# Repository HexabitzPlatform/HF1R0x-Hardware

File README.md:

# HF1R0x-Hardware
Hexabitz Raspberry Pi Interface Module Hardware Design

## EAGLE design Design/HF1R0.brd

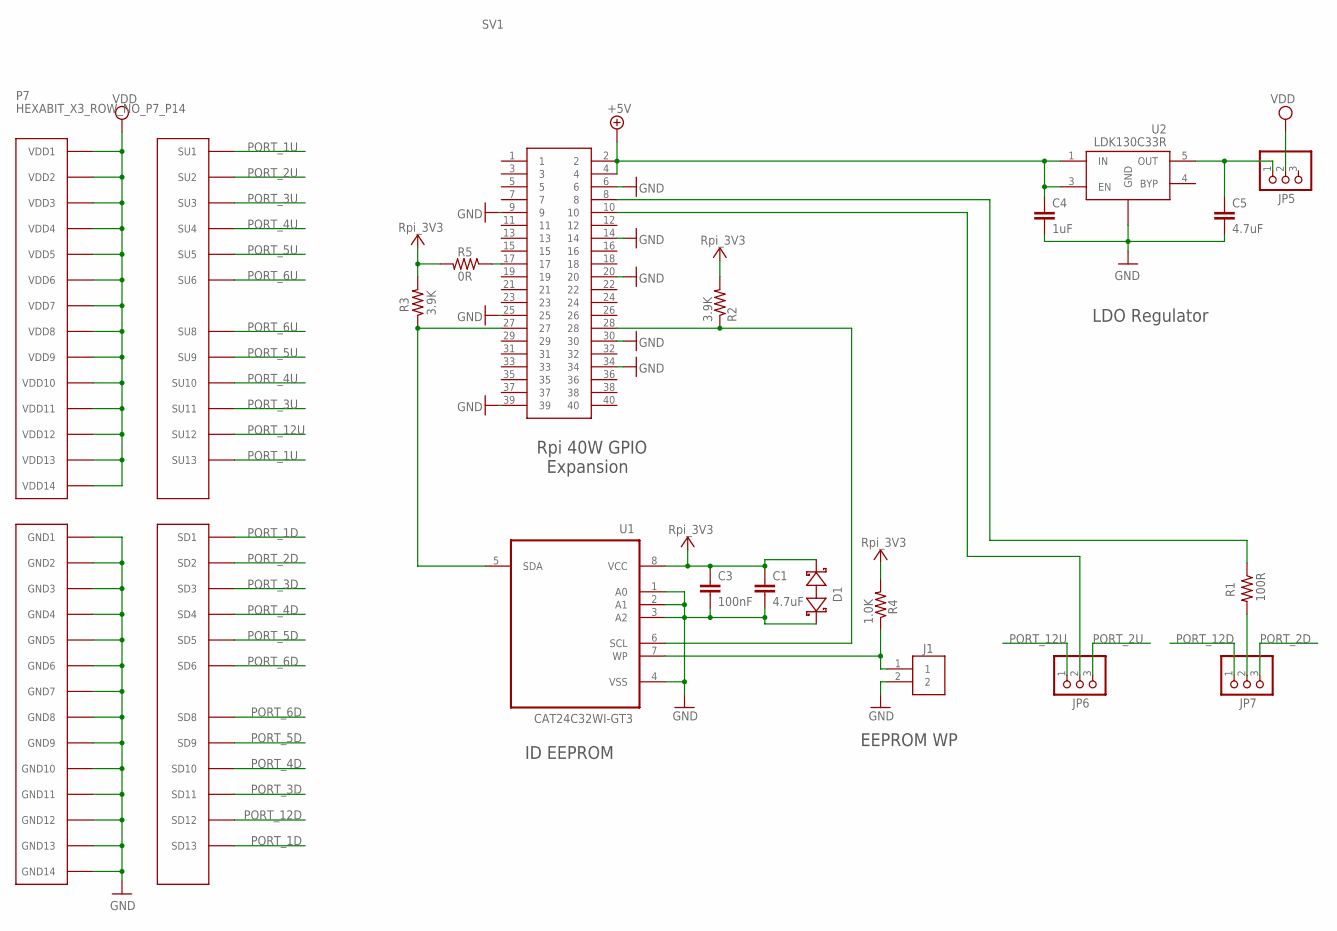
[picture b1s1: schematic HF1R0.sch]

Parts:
C1, C5: 4.7uF; C-0805
C3: 100nF; C-0603; TOLERANCE 10V; VOLTAGE_RATING 10%; MPN C0603C104K8RACTU
C4: 1uF; C-0805
D1: BOURNS_CDSOD323-T03SCBOURNS_CDSOD323-T03SC_0_0; BOURNS_CDSOD323-T03SC_0
J1: 3-644456-2; TE_3-644456-2
JP5, JP6, JP7: PINHD-1X3; 1X03
P7: HEXABIT_X3_ROW_NO_P7_P14
R1: 100R; R-0603; TOLERANCE 1%; MPN ERJ-PA3F1000V
R2, R3: 3.9K; R-0603; TOLERANCE 1%; MPN CRCW06033K90FKEA
R4: 1.0K; R-0603; TOLERANCE 1%; MPN ERJ-3EKF1001V
R5: 0R; R-0603; TOLERANCE 1%; MPN CRCW06033K90FKEA
SV1: PPTC202LFBN-RC; RHDR40W64P254X254_2X20_5105X50; MPN1 PPTC202LFBN-RC
TRIMBLE-LOGO2: HEXABITZ-LOGO
U1: CAT24C32WI-GT3; SOIC127P600X175-8N
U2: LDK130C33R; SOT65P210X110-5N

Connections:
+3V3: C1.1, C3.1, D1.2 (C), R2.2, R3.2, R4.2, R5.2, U1.8 (VCC)
+5V: C4.1, SV1.2, SV1.4, U2.1 (IN), U2.3 (EN)
GND: C1.2, C3.2, C4.2, C5.2, D1.1 (A), J1.2, P7.PAD_PD15 (GND1), P7.PAD_PD16 (GND2), P7.PAD_PD17 (GND3), P7.PAD_PD18 (GND4), P7.PAD_PD19 (GND5), P7.PAD_PD20 (GND6), P7.PAD_PD21 (GND7), P7.PAD_PD22 (GND8), P7.PAD_PD23 (GND9), P7.PAD_PD24 (GND10), P7.PAD_PD25 (GND11), P7.PAD_PD26 (GND12), P7.PAD_PD27 (GND13), P7.PAD_PD28 (GND14), SV1.6, SV1.9, SV1.14, SV1.20, SV1.25, SV1.30, SV1.34, SV1.39, U1.1 (A0), U1.2 (A1), U1.3 (A2), U1.4 (VSS), U2.2 (GND)
ID_SC: R2.1, SV1.28, U1.6 (SCL)
ID_SD: R3.1, SV1.27, U1.5 (SDA)
unnamed: JP7.2, R1.2
unnamed: J1.1, R4.1, U1.7 (WP)
unnamed: R5.1, SV1.17
unnamed: C5.1, JP5.1, U2.5 (OUT)
PORT_1D: P7.PAD_PD1 (SD1), P7.PAD_PD13 (SD13)
PORT_1U: P7.PAD_PU1 (SU1), P7.PAD_PU13 (SU13)
PORT_2D: JP7.3, P7.PAD_PD2 (SD2)
PORT_2U: JP6.3, P7.PAD_PU2 (SU2)
PORT_3D: P7.PAD_PD3 (SD3), P7.PAD_PD11 (SD11)
PORT_3U: P7.PAD_PU3 (SU3), P7.PAD_PU11 (SU11)
PORT_4D: P7.PAD_PD4 (SD4), P7.PAD_PD10 (SD10)
PORT_4U: P7.PAD_PU4 (SU4), P7.PAD_PU10 (SU10)
PORT_5D: P7.PAD_PD5 (SD5), P7.PAD_PD9 (SD9)
PORT_5U: P7.PAD_PU5 (SU5), P7.PAD_PU9 (SU9)
PORT_6D: P7.PAD_PD6 (SD6), P7.PAD_PD8 (SD8)
PORT_6U: P7.PAD_PU6 (SU6), P7.PAD_PU8 (SU8)
PORT_12D: JP7.1, P7.PAD_PD12 (SD12)
PORT_12U: JP6.1, P7.PAD_PU12 (SU12)
RXD0: JP6.2, SV1.10
TXD0: R1.1, SV1.8
VDD: JP5.2, P7.PAD_PU15 (VDD1), P7.PAD_PU16 (VDD2), P7.PAD_PU17 (VDD3), P7.PAD_PU18 (VDD4), P7.PAD_PU19 (VDD5), P7.PAD_PU20 (VDD6), P7.PAD_PU21 (VDD7), P7.PAD_PU22 (VDD8), P7.PAD_PU23 (VDD9), P7.PAD_PU24 (VDD10), P7.PAD_PU25 (VDD11), P7.PAD_PU26 (VDD12), P7.PAD_PU27 (VDD13), P7.PAD_PU28 (VDD14)

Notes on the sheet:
Rpi 40W GPIO Expansion
ID EEPROM
EEPROM WP
LDO Regulator

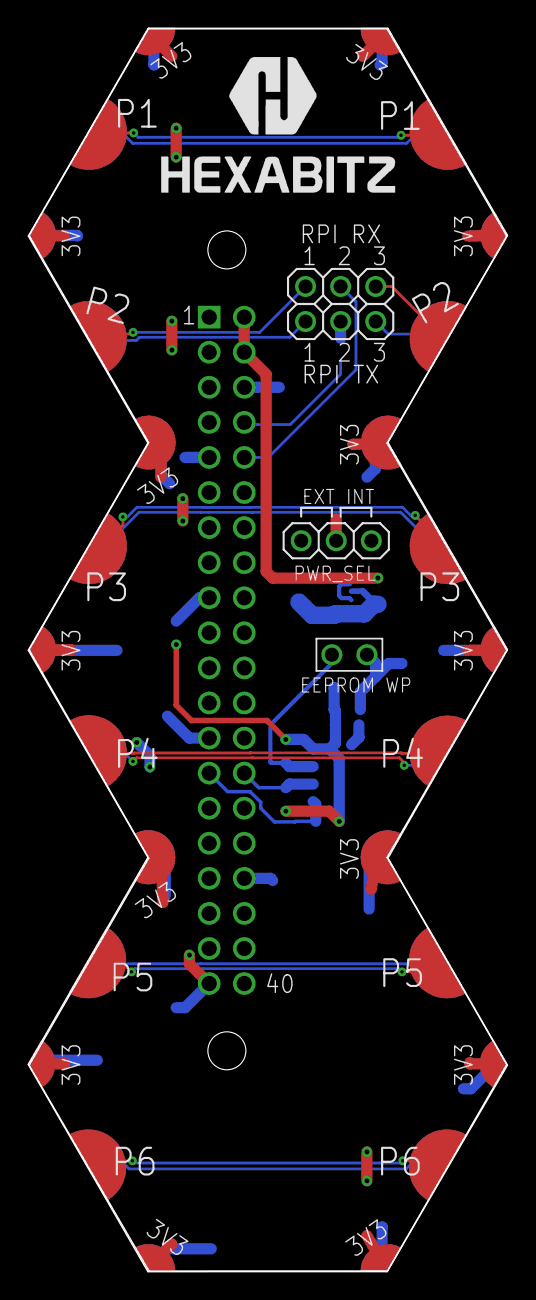
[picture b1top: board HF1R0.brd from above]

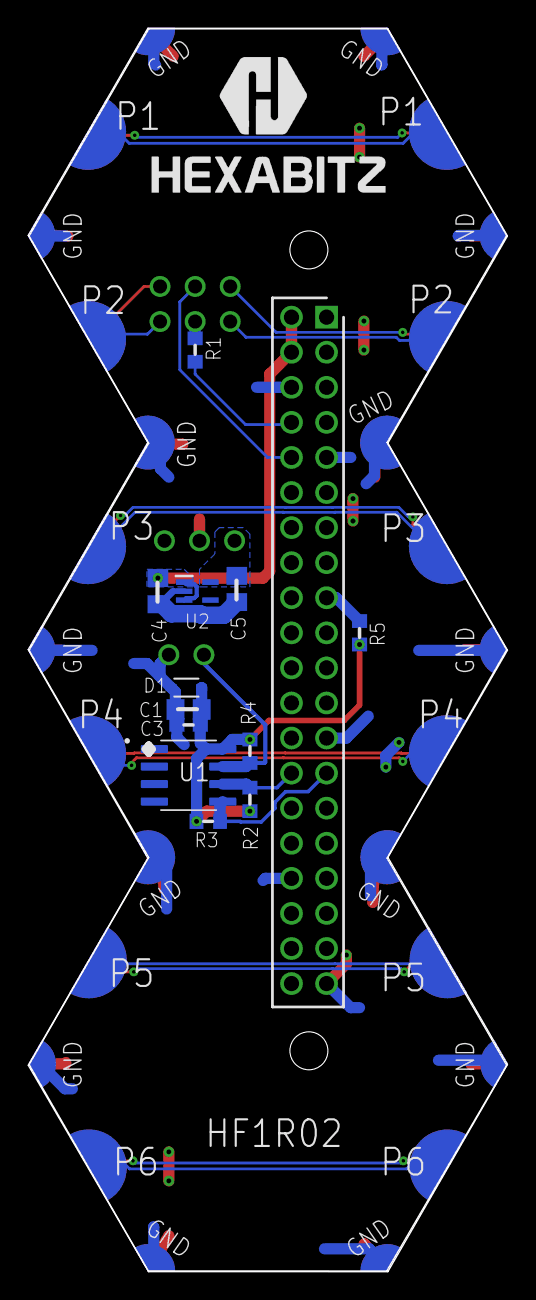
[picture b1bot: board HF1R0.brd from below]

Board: 2 copper layers, 34.7 x 90.0 mm, 19 parts (12 on the bottom side), 26 nets.

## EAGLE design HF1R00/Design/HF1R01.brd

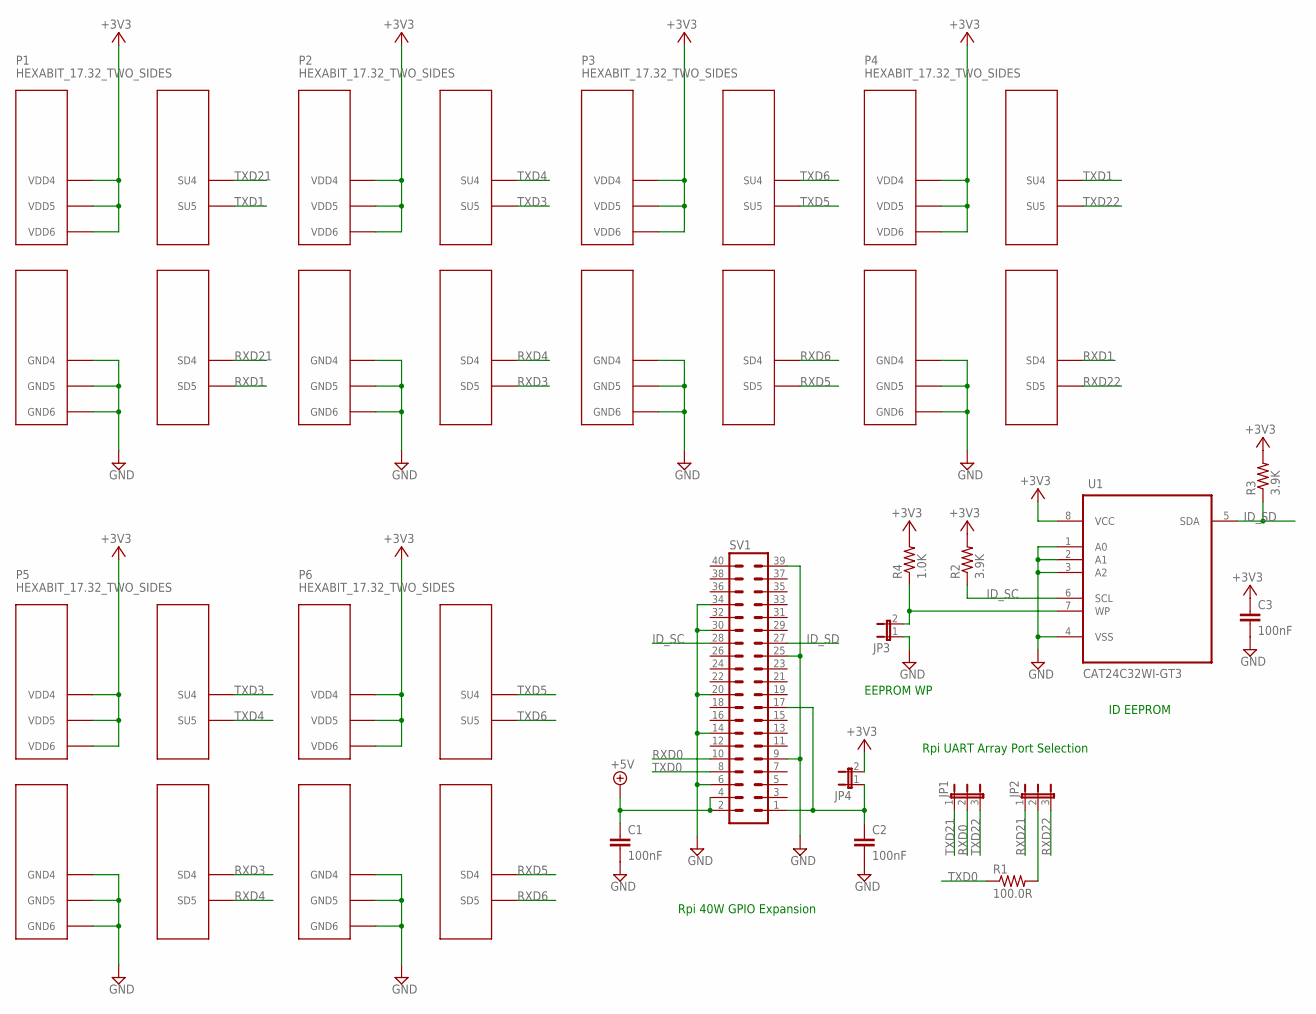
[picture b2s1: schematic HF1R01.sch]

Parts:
C1, C2, C3: 100nF; C-0603; TOLERANCE 10V; VOLTAGE_RATING 10%; MPN C0603C104K8RACTU
JP1, JP2: 61300311121; JP2; MPN 61300311121
JP3, JP4: 61300211121; JP1; MPN 61300211121
P1, P2, P3, P4, P5, P6: HEXABIT_17.32_TWO_SIDES
R1: 100.0R; R-0603; TOLERANCE 1%; MPN ERJ-PA3F1000V
R2, R3: 3.9K; R-0603; TOLERANCE 1%; MPN CRCW06033K90FKEA
R4: 1.0K; R-0603; TOLERANCE 1%; MPN ERJ-3EKF1001V
SV1: PPTC202LFBN-RC; MA20-2; MPN PPTC202LFBN-RC
U1: CAT24C32WI-GT3; SOIC127P600X175-8N

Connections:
+3V3: C3.1, JP4.2, P1.PAD_PU10 (VDD4), P1.PAD_PU11 (VDD5), P1.PAD_PU12 (VDD6), P2.PAD_PU10 (VDD4), P2.PAD_PU11 (VDD5), P2.PAD_PU12 (VDD6), P3.PAD_PU10 (VDD4), P3.PAD_PU11 (VDD5), P3.PAD_PU12 (VDD6), P4.PAD_PU10 (VDD4), P4.PAD_PU11 (VDD5), P4.PAD_PU12 (VDD6), P5.PAD_PU10 (VDD4), P5.PAD_PU11 (VDD5), P5.PAD_PU12 (VDD6), P6.PAD_PU10 (VDD4), P6.PAD_PU11 (VDD5), P6.PAD_PU12 (VDD6), R2.2, R3.2, R4.2, U1.8 (VCC)
+5V: C1.1, SV1.2, SV1.4
GND: C1.2, C2.2, C3.2, JP3.1, P1.PAD_PD10 (GND4), P1.PAD_PD11 (GND5), P1.PAD_PD12 (GND6), P2.PAD_PD10 (GND4), P2.PAD_PD11 (GND5), P2.PAD_PD12 (GND6), P3.PAD_PD10 (GND4), P3.PAD_PD11 (GND5), P3.PAD_PD12 (GND6), P4.PAD_PD10 (GND4), P4.PAD_PD11 (GND5), P4.PAD_PD12 (GND6), P5.PAD_PD10 (GND4), P5.PAD_PD11 (GND5), P5.PAD_PD12 (GND6), P6.PAD_PD10 (GND4), P6.PAD_PD11 (GND5), P6.PAD_PD12 (GND6), SV1.6, SV1.9, SV1.14, SV1.20, SV1.25, SV1.30, SV1.34, SV1.39, U1.1 (A0), U1.2 (A1), U1.3 (A2), U1.4 (VSS)
ID_SC: R2.1, SV1.28, U1.6 (SCL)
ID_SD: R3.1, SV1.27, U1.5 (SDA)
unnamed: JP2.2, R1.2
unnamed: JP3.2, R4.1, U1.7 (WP)
unnamed: C2.1, JP4.1, SV1.1, SV1.17
RXD0: JP1.2, SV1.10
RXD1: P1.PAD_PD5 (SD5), P4.PAD_PD4 (SD4)
RXD3: P2.PAD_PD5 (SD5), P5.PAD_PD4 (SD4)
RXD4: P2.PAD_PD4 (SD4), P5.PAD_PD5 (SD5)
RXD5: P3.PAD_PD5 (SD5), P6.PAD_PD4 (SD4)
RXD6: P3.PAD_PD4 (SD4), P6.PAD_PD5 (SD5)
RXD21: JP2.1, P1.PAD_PD4 (SD4)
RXD22: JP2.3, P4.PAD_PD5 (SD5)
TXD0: R1.1, SV1.8
TXD1: P1.PAD_PU5 (SU5), P4.PAD_PU4 (SU4)
TXD3: P2.PAD_PU5 (SU5), P5.PAD_PU4 (SU4)
TXD4: P2.PAD_PU4 (SU4), P5.PAD_PU5 (SU5)
TXD5: P3.PAD_PU5 (SU5), P6.PAD_PU4 (SU4)
TXD6: P3.PAD_PU4 (SU4), P6.PAD_PU5 (SU5)
TXD21: JP1.1, P1.PAD_PU4 (SU4)
TXD22: JP1.3, P4.PAD_PU5 (SU5)

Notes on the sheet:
Rpi UART Array Port Selection
Rpi 40W GPIO Expansion
ID EEPROM
EEPROM WP

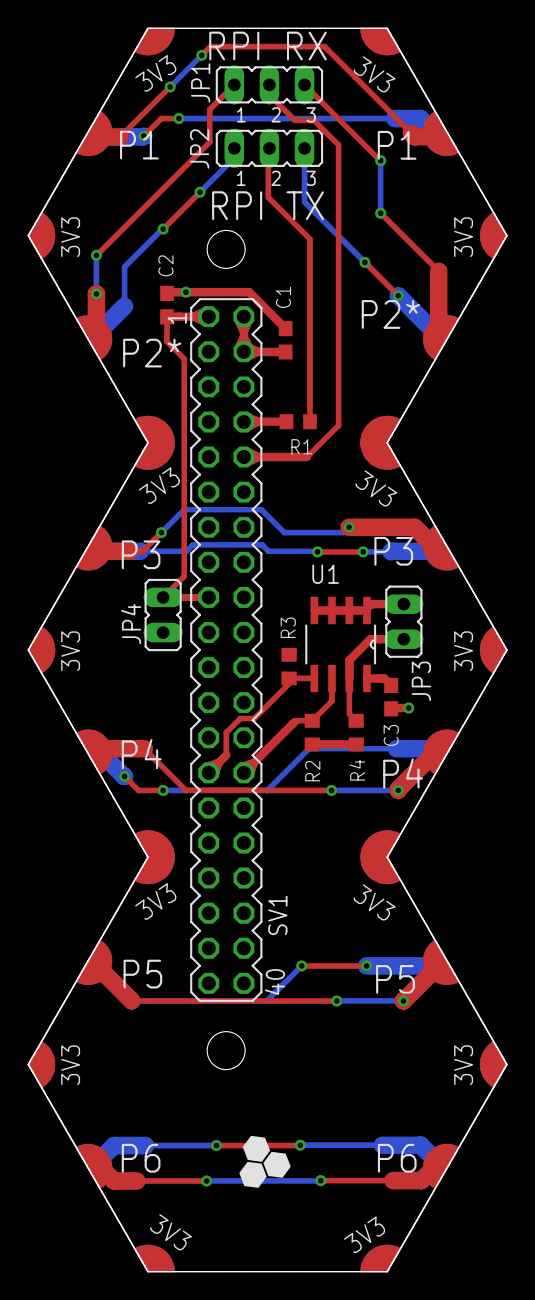
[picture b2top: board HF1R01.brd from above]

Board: 2 copper layers, 34.6 x 90.0 mm, 19 parts (0 on the bottom side), 24 nets.

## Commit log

2019-05-23 First release rev 0
2020-02-27 Update schematics and BOM
2021-04-28 - Added a header pin to isolate the 3.3v between ras and modules.. - Changed to Rev1.. - Updated BOM and Document..
2024-05-10 Fix bom
2025-01-06 -The final design, all done.
